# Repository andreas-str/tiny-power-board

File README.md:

# tiny-power-board

This is a full schematic and board for a tiny MOSFET power controller. It  was designed for the lightsaber project as I had very specific power and space requirements (over 10A at 4V)

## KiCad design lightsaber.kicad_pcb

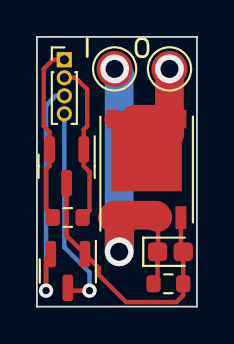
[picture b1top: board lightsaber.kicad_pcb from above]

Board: 2 copper layers, 8.9 x 15.0 mm, 9 parts (0 on the bottom side), 7 nets.

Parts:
C1: 100nF; CP_EIA-1608-10_AVX-L
D1: BAT54C; SOT-23
I: Battery + In; TestPoint_Pad_D2.0mm
J1: GPIO; PinHeader_1x04_P1.00mm_Vertical
O: Battery + Out; TestPoint_Pad_D2.0mm
Q1: SI7149ADP-T1-GE3; PowerPAK_SO-8_Single
Q2: IRLML0030TRPBF; SOT-23
R1, R2: 100K; R_0603_1608Metric

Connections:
GND: J1.1, Q2.2 (S), R2.2
unnamed: C1.1, I.1, Q1.1 (S), Q1.2 (S), Q1.3 (S), R1.1
unnamed: J1.2, Q2.1 (G), R2.1
unnamed: D1.2, J1.3
unnamed: D1.3, J1.4
unnamed: O.1, Q1.5 (D)
unnamed: C1.2, D1.1, Q1.4 (G), Q2.3 (D), R1.2
